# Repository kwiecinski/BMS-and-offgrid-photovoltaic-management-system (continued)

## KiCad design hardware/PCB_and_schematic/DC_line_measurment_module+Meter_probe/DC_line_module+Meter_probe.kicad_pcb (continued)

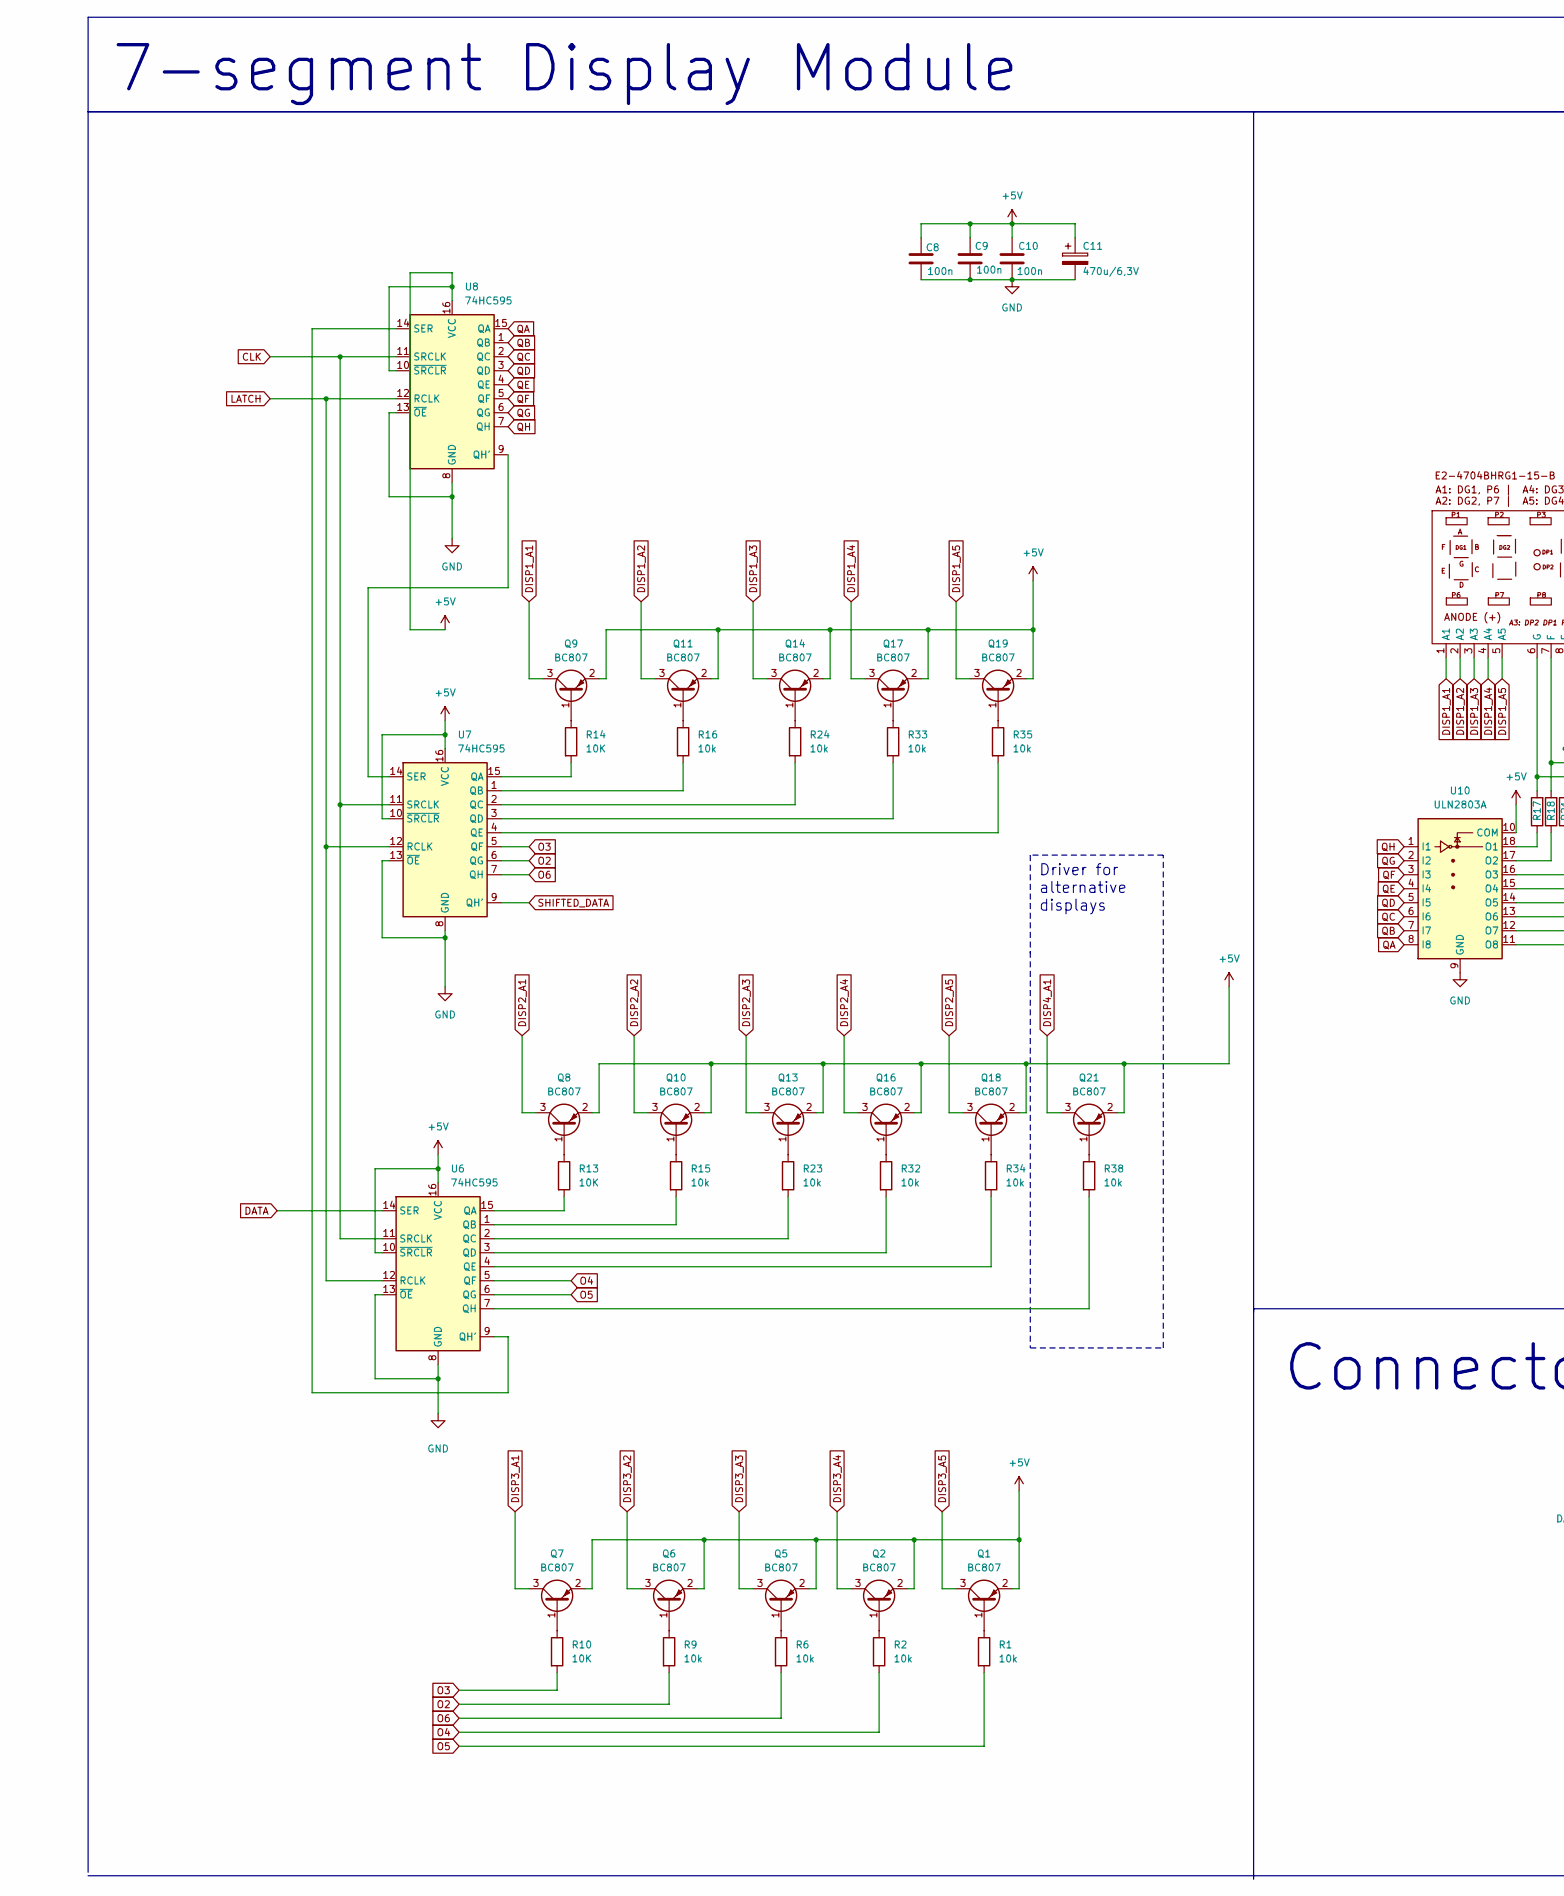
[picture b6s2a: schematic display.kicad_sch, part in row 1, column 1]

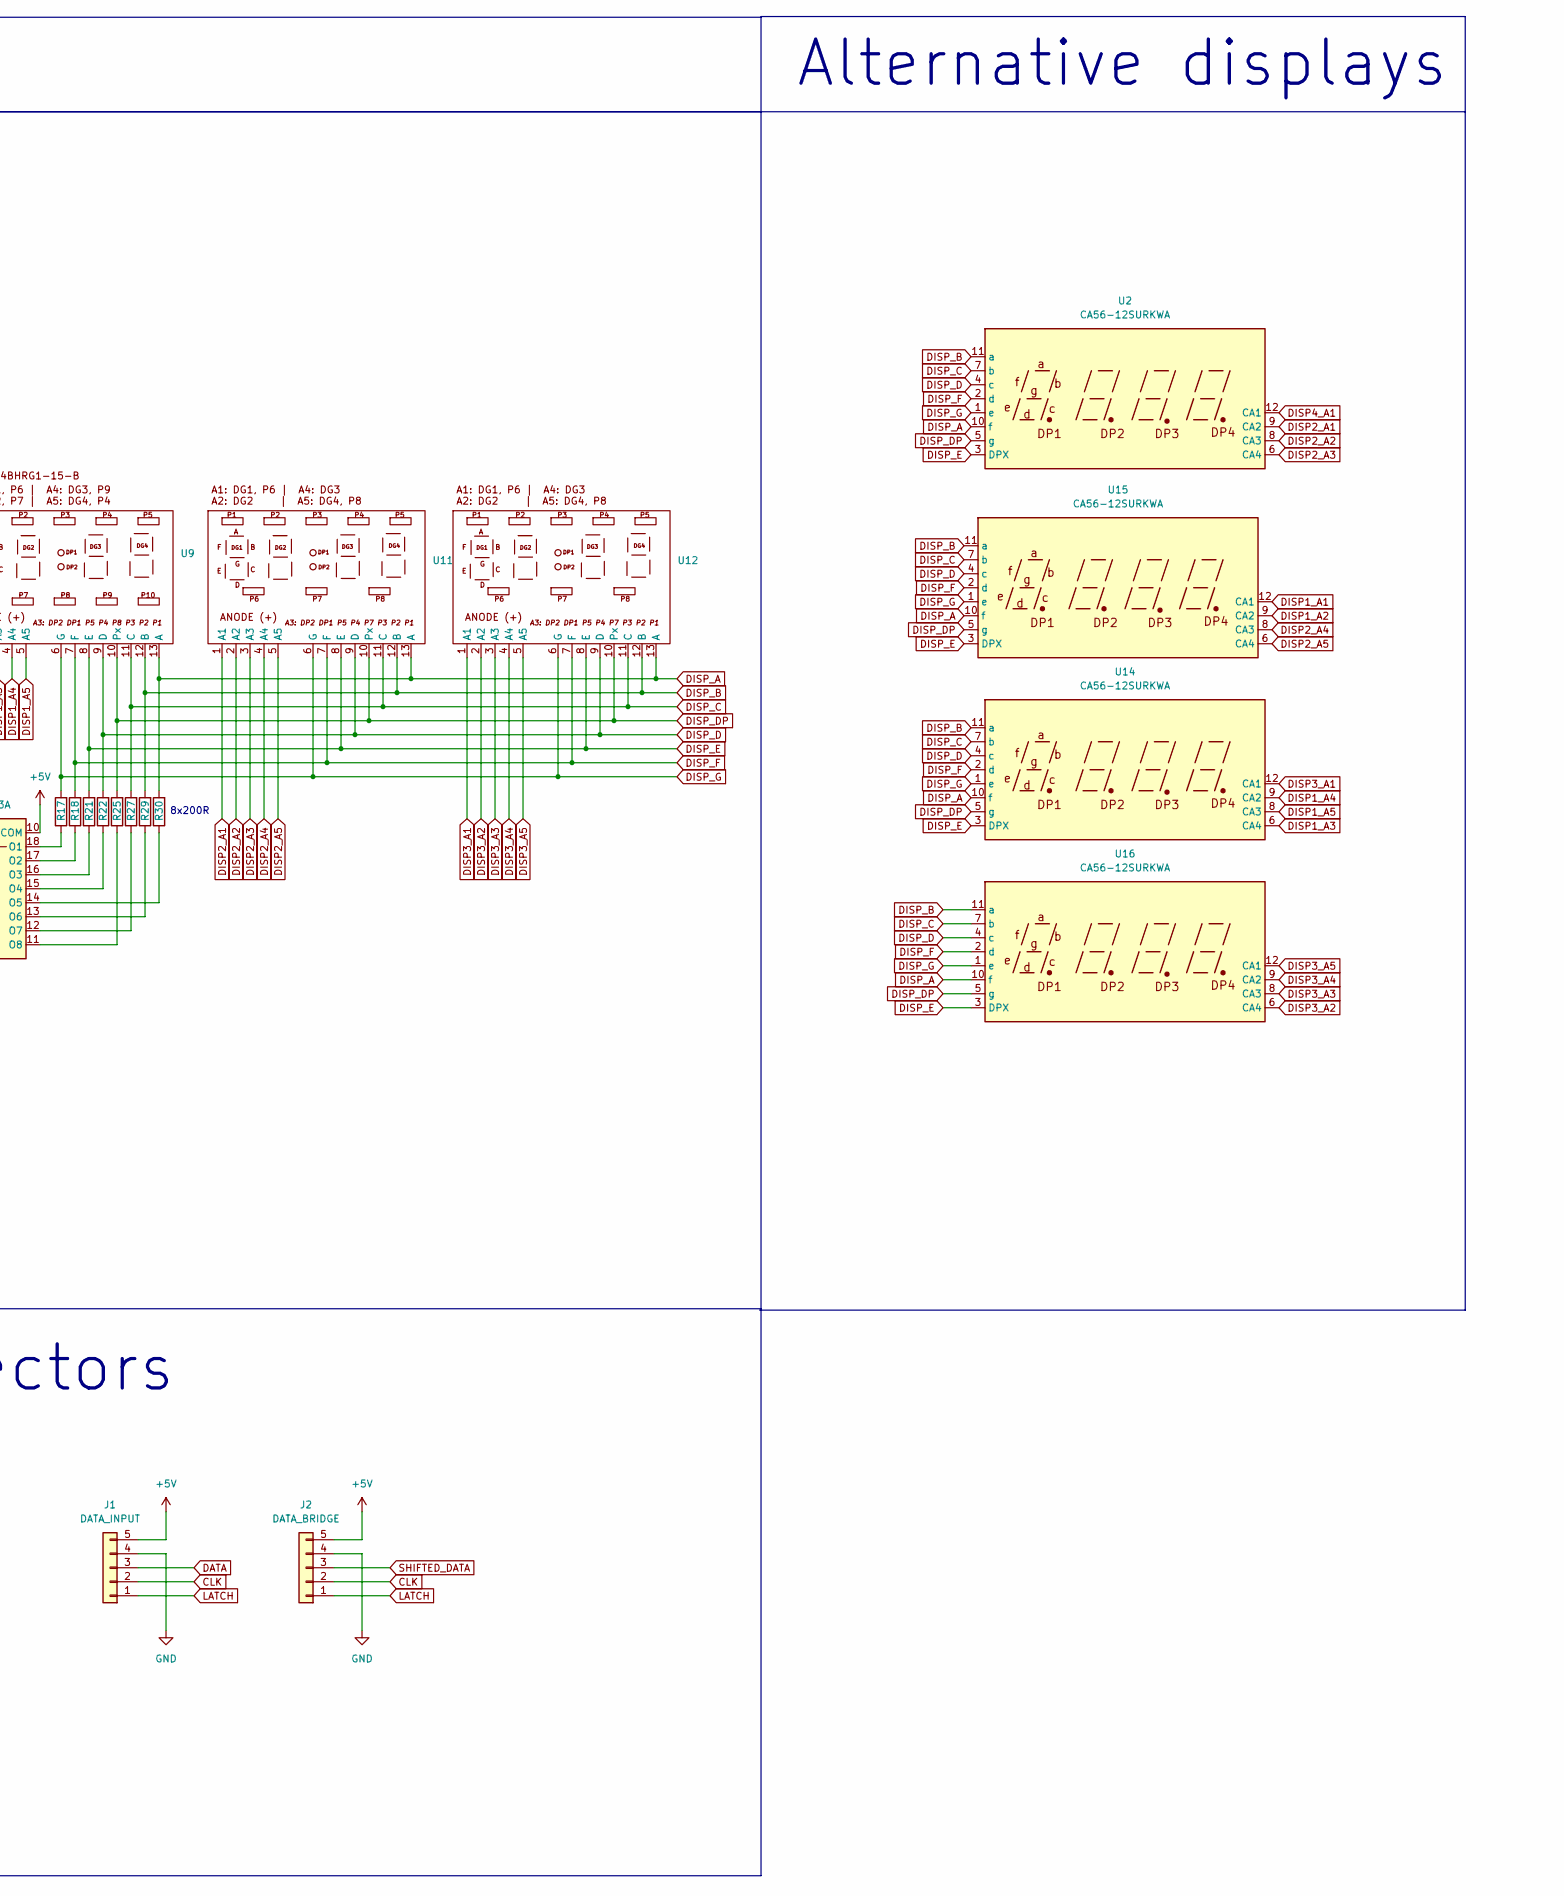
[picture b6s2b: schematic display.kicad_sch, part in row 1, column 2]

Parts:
C8, C9, C10: 100n; C_0805_2012Metric
C11: 470u/6,3V; CP_Radial_D10.0mm_P2.50mm
J1: DATA_INPUT; JST_XH_B5B-XH-A_1x05_P2.54mm_Vertical
J2: DATA_BRIDGE; JST_XH_B5B-XH-A_1x05_P2.54mm_Vertical
Q1, Q2, Q5, Q6, Q7, Q8, Q9, Q10, Q11, Q13, Q14, Q16, Q17, Q18, Q19, Q21: BC807; SOT-23
R1, R2, R6, R9, R15, R16, R23, R24, R32, R33, R34, R35, R38: 10k; R_0805_2012Metric_Pad1.20x1.40mm_HandSolder
R10, R13, R14: 10K; R_0805_2012Metric_Pad1.20x1.40mm_HandSolder
R17, R18, R21, R22, R25, R27, R29, R30: 200R; R_0805_2012Metric_Pad1.20x1.40mm_HandSolder
U2, U14, U15, U16: CA56-12SURKWA; 4-digit-7-segment-display_smd
U6, U7, U8: 74HC595; SO-16_3.9x9.9mm_P1.27mm
U9, U11, U12: JZG_E5627BRG-1_7_SEGMENT_DISPLAY
U10: ULN2803A; SOIC-18W_7.5x11.6mm_P1.27mm

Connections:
+5V: C8.1, C9.1, C10.1, C11.1, J1.5, J2.5, Q1.2 (E), Q2.2 (E), Q5.2 (E), Q6.2 (E), Q7.2 (E), Q8.2 (E), Q9.2 (E), Q10.2 (E), Q11.2 (E), Q13.2 (E), Q14.2 (E), Q16.2 (E), Q17.2 (E), Q18.2 (E), Q19.2 (E), Q21.2 (E), U6.10 (~SRCLR), U6.16 (VCC), U7.10 (~SRCLR), U7.16 (VCC), U8.10 (~SRCLR), U8.16 (VCC), U10.10 (COM); also elsewhere on the board
CLK: J1.2, J2.2, U6.11 (SRCLK), U7.11 (SRCLK), U8.11 (SRCLK)
DATA: J1.3, U6.14 (SER)
DISP1_A1: Q9.3 (C), U9.1 (A1), U15.12 (CA1)
DISP1_A2: Q11.3 (C), U9.2 (A2), U15.9 (CA2)
DISP1_A3: Q14.3 (C), U9.3 (A3), U14.6 (CA4)
DISP1_A4: Q17.3 (C), U9.4 (A4), U14.9 (CA2)
DISP1_A5: Q19.3 (C), U9.5 (A5), U14.8 (CA3)
DISP2_A1: Q8.3 (C), U2.9 (CA2), U11.1 (A1)
DISP2_A2: Q10.3 (C), U2.8 (CA3), U11.2 (A2)
DISP2_A3: Q13.3 (C), U2.6 (CA4), U11.3 (A3)
DISP2_A4: Q16.3 (C), U11.4 (A4), U15.8 (CA3)
DISP2_A5: Q18.3 (C), U11.5 (A5), U15.6 (CA4)
DISP3_A1: Q7.3 (C), U12.1 (A1), U14.12 (CA1)
DISP3_A2: Q6.3 (C), U12.2 (A2), U16.6 (CA4)
DISP3_A3: Q5.3 (C), U12.3 (A3), U16.8 (CA3)
DISP3_A4: Q2.3 (C), U12.4 (A4), U16.9 (CA2)
DISP3_A5: Q1.3 (C), U12.5 (A5), U16.12 (CA1)
DISP4_A1: Q21.3 (C), U2.12 (CA1)
DISP_A: R30.2, U2.10 (f), U9.13 (A), U11.13 (A), U12.13 (A), U14.10 (f), U15.10 (f), U16.10 (f)
DISP_B: R29.2, U2.11 (a), U9.12 (B), U11.12 (B), U12.12 (B), U14.11 (a), U15.11 (a), U16.11 (a)
DISP_C: R27.2, U2.7 (b), U9.11 (C), U11.11 (C), U12.11 (C), U14.7 (b), U15.7 (b), U16.7 (b)
DISP_D: R22.2, U2.4 (c), U9.9 (D), U11.9 (D), U12.9 (D), U14.4 (c), U15.4 (c), U16.4 (c)
DISP_DP: R25.2, U2.5 (g), U9.10 (Px), U11.10 (Px), U12.10 (Px), U14.5 (g), U15.5 (g), U16.5 (g)
DISP_E: R21.2, U2.3 (DPX), U9.8 (E), U11.8 (E), U12.8 (E), U14.3 (DPX), U15.3 (DPX), U16.3 (DPX)
DISP_F: R18.2, U2.2 (d), U9.7 (F), U11.7 (F), U12.7 (F), U14.2 (d), U15.2 (d), U16.2 (d)
DISP_G: R17.2, U2.1 (e), U9.6 (G), U11.6 (G), U12.6 (G), U14.1 (e), U15.1 (e), U16.1 (e)
GND: C8.2, C9.2, C10.2, C11.2, J1.4, J2.4, U6.8 (GND), U6.13 (~OE), U7.8 (GND), U7.13 (~OE), U8.8 (GND), U8.13 (~OE), U10.9 (GND); also elsewhere on the board
LATCH: J1.1, J2.1, U6.12 (RCLK), U7.12 (RCLK), U8.12 (RCLK)
unnamed: Q1.1 (B), R1.1
unnamed: Q2.1 (B), R2.1
unnamed: Q5.1 (B), R6.1
unnamed: Q6.1 (B), R9.1
unnamed: Q7.1 (B), R10.1
unnamed: Q8.1 (B), R13.1
unnamed: Q9.1 (B), R14.1
unnamed: Q10.1 (B), R15.1
unnamed: Q11.1 (B), R16.1
unnamed: Q13.1 (B), R23.1
unnamed: Q14.1 (B), R24.1
unnamed: Q16.1 (B), R32.1
unnamed: Q17.1 (B), R33.1
unnamed: Q18.1 (B), R34.1
unnamed: Q19.1 (B), R35.1
unnamed: Q21.1 (B), R38.1
unnamed: R13.2, U6.15 (QA)
unnamed: R15.2, U6.1 (QB)
unnamed: R23.2, U6.2 (QC)
unnamed: R32.2, U6.3 (QD)
unnamed: R34.2, U6.4 (QE)
unnamed: U6.9 (QH'), U8.14 (SER)
unnamed: R38.2, U6.7 (QH)
unnamed: R14.2, U7.15 (QA)
unnamed: R16.2, U7.1 (QB)
unnamed: R24.2, U7.2 (QC)
unnamed: R33.2, U7.3 (QD)
unnamed: R35.2, U7.4 (QE)
unnamed: U7.14 (SER), U8.9 (QH')
unnamed: R17.1, U10.18 (O1)
unnamed: R18.1, U10.17 (O2)
unnamed: R21.1, U10.16 (O3)
unnamed: R22.1, U10.15 (O4)
unnamed: R30.1, U10.14 (O5)
unnamed: R29.1, U10.13 (O6)
unnamed: R27.1, U10.12 (O7)
unnamed: R25.1, U10.11 (O8)
O2: R9.2, U7.6 (QG)
O3: R10.2, U7.5 (QF)
O4: R2.2, U6.5 (QF)
O5: R1.2, U6.6 (QG)
O6: R6.2, U7.7 (QH)
QA: U8.15 (QA), U10.8 (I8)
QB: U8.1 (QB), U10.7 (I7)
QC: U8.2 (QC), U10.6 (I6)
QD: U8.3 (QD), U10.5 (I5)
QE: U8.4 (QE), U10.4 (I4)
QF: U8.5 (QF), U10.3 (I3)
QG: U8.6 (QG), U10.2 (I2)
QH: U8.7 (QH), U10.1 (I1)
SHIFTED_DATA: J2.3, U7.9 (QH')

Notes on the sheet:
Alternative displays
Driver for alternative displays
7-segment Display Module
Connectors
8x200R

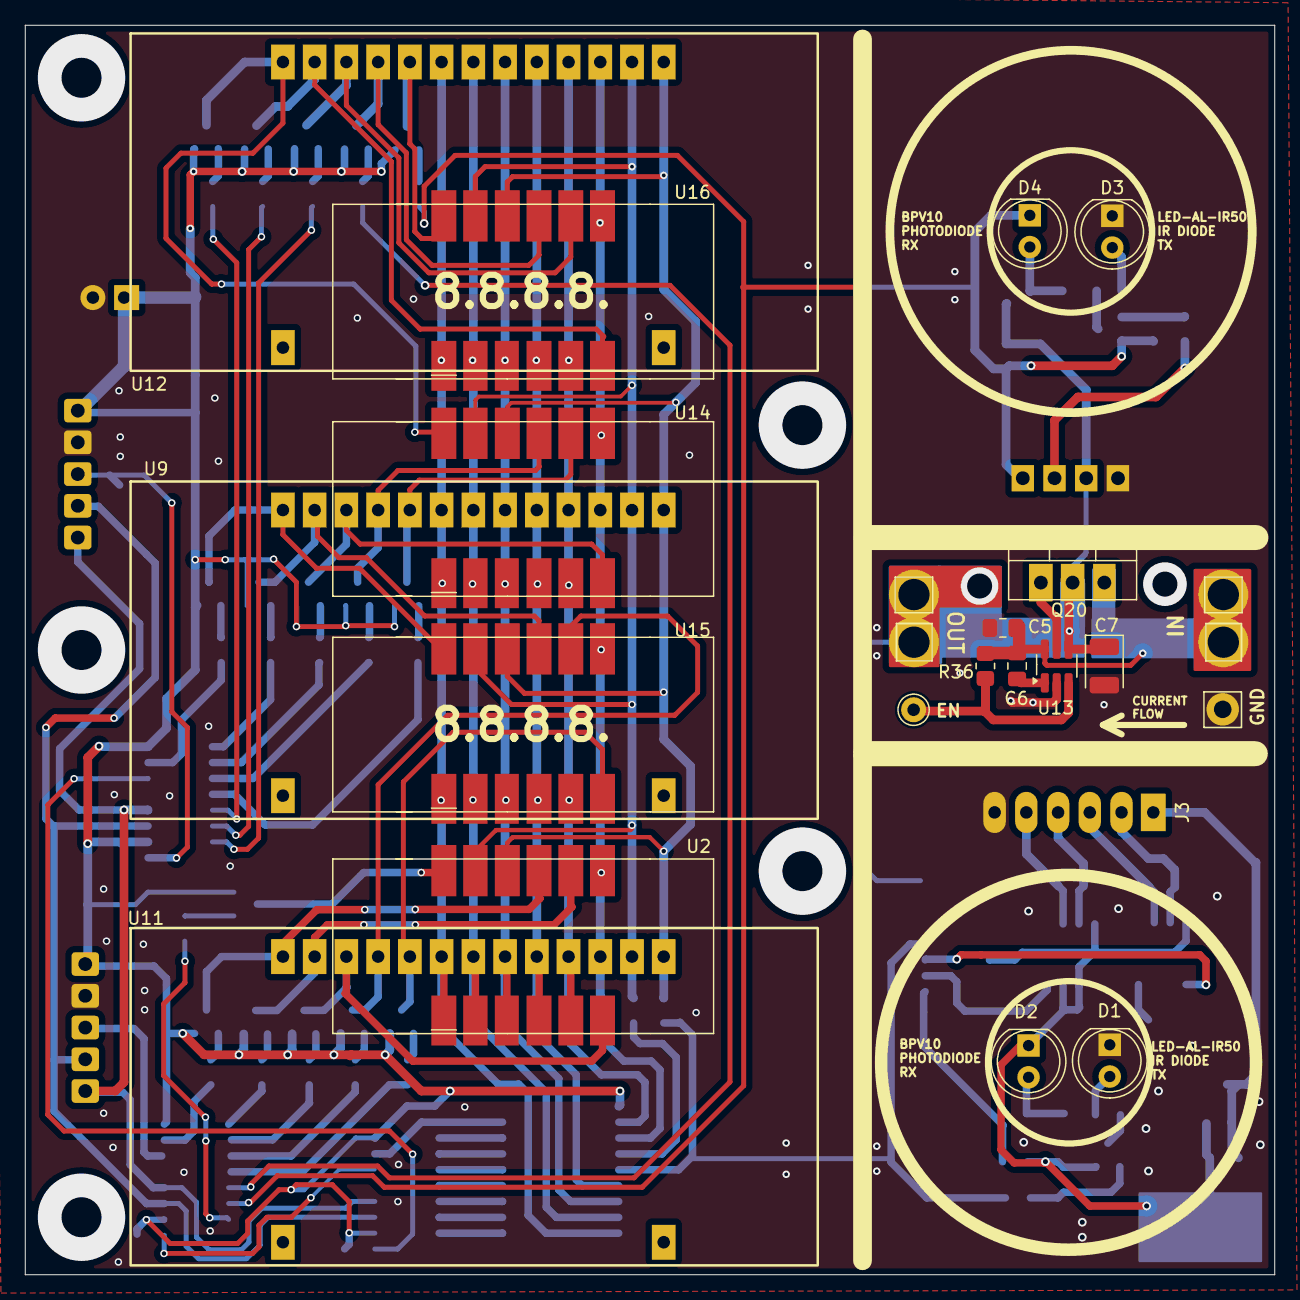
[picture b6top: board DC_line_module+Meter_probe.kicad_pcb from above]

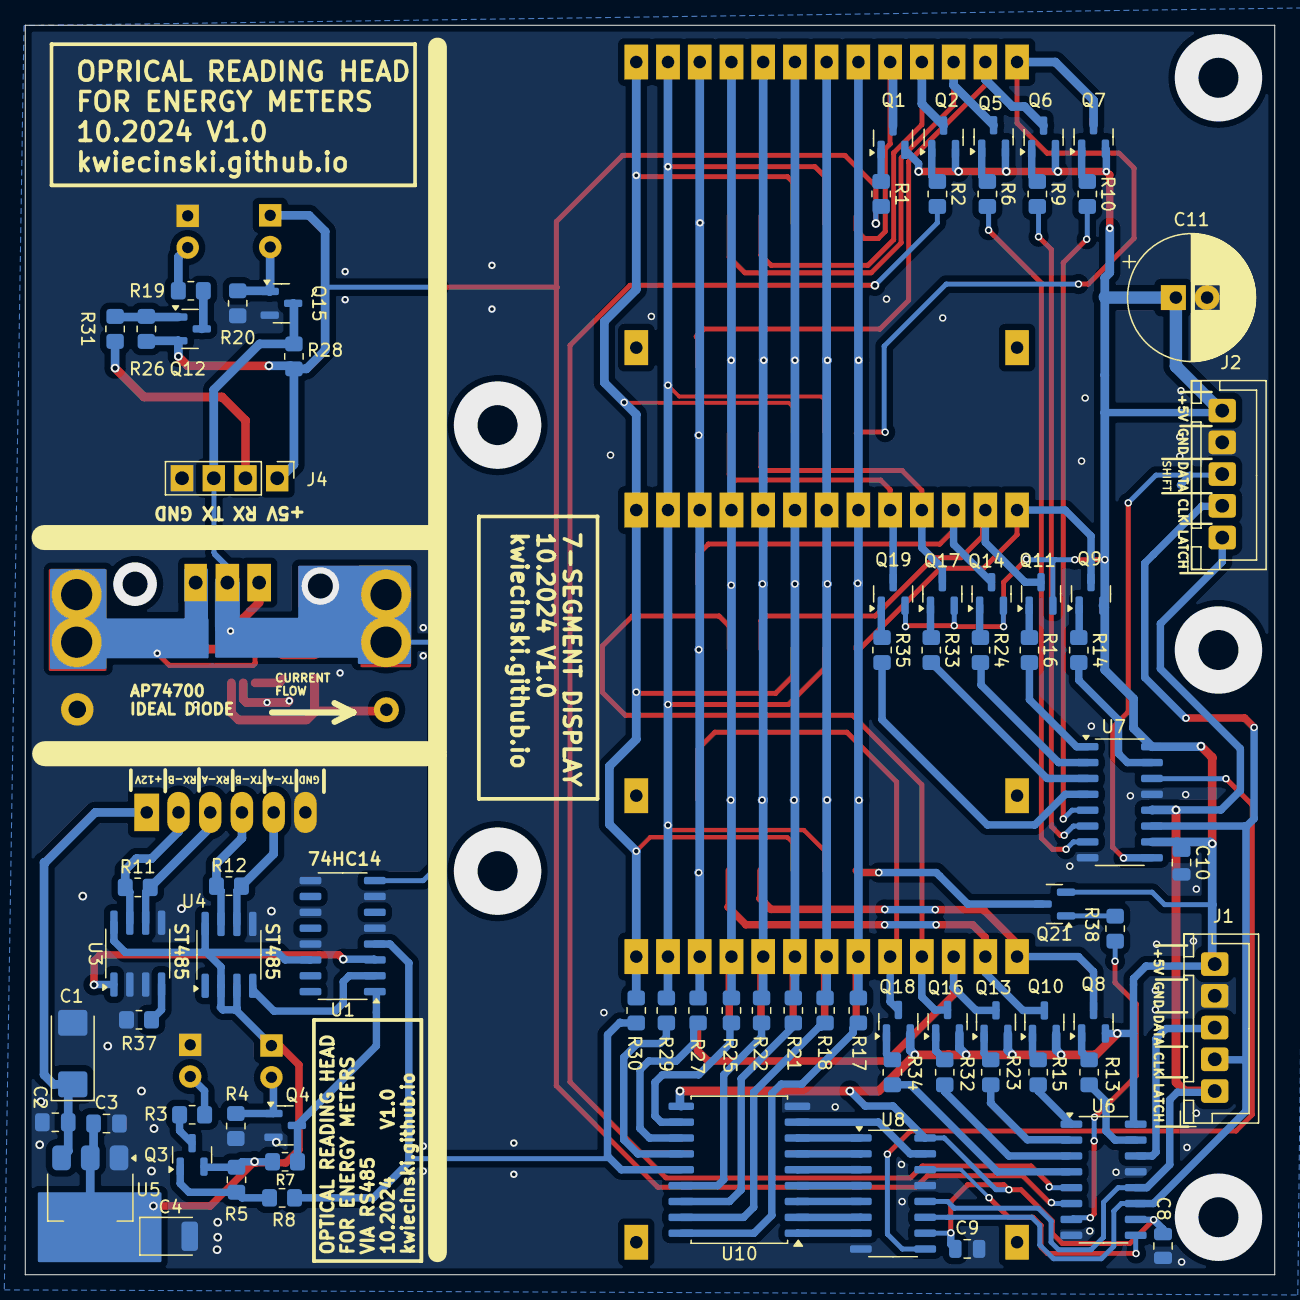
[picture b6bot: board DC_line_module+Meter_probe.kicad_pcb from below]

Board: 2 copper layers, 100.0 x 100.0 mm, 100 parts (76 on the bottom side), 106 nets.

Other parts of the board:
C5, C6: 100n; C_0805_2012Metric_Pad1.18x1.45mm_HandSolder
C7: 22u; CP_EIA-3528-21_Kemet-B
J5, J5#2: IN; Pin_D1.4mm_L8.5mm_W2.8mm_FlatFork
J6: GND; Pin_D1.4mm_L8.5mm_W2.8mm_FlatFork
J7: GND; Pin_D1.0mm_L10.0mm
J8, J8#2: OUT; Pin_D1.4mm_L8.5mm_W2.8mm_FlatFork
Q20: IRF540N; TO-220-3_Vertical
R36: 1k; R_0805_2012Metric_Pad1.20x1.40mm_HandSolder
U13: AP74700; SOT-23-6_Handsoldering

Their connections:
GND: C5.2, C7.2, J6.1, U13.2 (GND); also elsewhere on the board
unnamed: C5.1, C6.1, J5.1, J5#2.1, Q20.3 (S), R36.2, U13.6 (ANODE)
unnamed: J7.1, R36.1, U13.3 (EN)
unnamed: C7.1, J8.1, J8#2.1, Q20.2 (D), U13.4 (CATHODE)
unnamed: Q20.1 (G), U13.5 (GATE)
unnamed: C6.2, U13.1 (VCP)

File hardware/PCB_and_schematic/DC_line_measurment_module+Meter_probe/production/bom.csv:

Designator,Footprint,Quantity,Value,LCSC Part #
C1,CP_EIA-6032-28_Kemet-C,1,100u,
"C10, C2, C3, C5, C6, C8, C9",0805,7,100n,
C11,CP_Radial_D10.0mm_P2.50mm,1,"470u/6,3V",
"C4, C7",CP_EIA-3528-21_Kemet-B,2,22u,
"D1, D3",LED_D5.0mm,2,LED-AL-IR50,
"D2, D4",LED_D5.0mm,2,BPV10,
J1,JST_XH_B5B-XH-A_1x05_P2.54mm_Vertical,1,DATA_INPUT,
J2,JST_XH_B5B-XH-A_1x05_P2.54mm_Vertical,1,DATA_BRIDGE,
J3,Pin_Header_Straight_1x06_Pitch2.54mm,1,POWER_RS485,
J4,PinHeader_1x04_P2.54mm_Vertical,1,PROBE_CONN,
"J5_2, J5",Pin_D1.4mm_L8.5mm_W2.8mm_FlatFork,2,IN,
J6,Pin_D1.4mm_L8.5mm_W2.8mm_FlatFork,1,GND,
J7,Pin_D1.0mm_L10.0mm,1,GND,
"J8_2, J8",Pin_D1.4mm_L8.5mm_W2.8mm_FlatFork,2,OUT,
"Q1, Q10, Q11, Q12, Q13, Q14, Q16, Q17, Q18, Q19, Q2, Q21, Q3, Q5, Q6, Q7, Q8, Q9",SOT-23,18,BC807,
"Q15, Q4",SOT-23,2,BC817,
Q20,TO-220-3_Vertical,1,IRF540N,
"R1, R10, R13, R14, R15, R16, R2, R23, R24, R32, R33, R34, R35, R37, R38, R6, R9",0805,17,10k,
"R11, R12",0805,2,120R,
"R17, R18, R21, R22, R25, R27, R29, R30",0805,8,200R,
"R19, R3",0805,2,160R,
"R20, R26, R4, R5",0805,4,47k,
"R28, R7",0805,2,22k,
"R31, R36, R8",0805,3,1k,
U1,SO-16_3.9x9.9mm_P1.27mm,1,74HC14,
U10,SOIC-18W_7.5x11.6mm_P1.27mm,1,ULN2803A,
"U11, U12, U9",JZG_E5627BRG-1_7_SEGMENT_DISPLAY,3,~,
U13,SOT-23-6_Handsoldering,1,AP74700,
"U14, U15, U16, U2",4-digit-7-segment-display_smd,4,CA56-12SURKWA,
"U3, U4",SOIC-8_3.9x4.9mm_P1.27mm,2,ST485EBDR,
U5,SOT-223-3_TabPin2,1,AMS1117-5.0,
"U6, U7, U8",SO-16_3.9x9.9mm_P1.27mm,3,74HC595,
